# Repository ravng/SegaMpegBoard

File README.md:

# SegaMpegBoard!

Drop in replacement board for Sega Model 3 Mpeg board.
Tested on Scud Race but can't see why it would not work in other aracdes with the same mpeg board.

It uses the cheap DFPlayer MP3 module for soundtrack files and attiny84 for the communication.

A jumper is used to select different soundtracks (folders). 
Folder 1-4 plays the same sound track for each race track every time, while folder 5 will play songs in random order. 
If no jumper installed it will use folder "01", see source for details. 

IMPORTANT NOTE!
The attiny might need a clock calibration to work. 
I supposed it would be smart to add an external clock, but I didn't.
Fell free to modify the design yourself or search the web for attiny clock calibration.

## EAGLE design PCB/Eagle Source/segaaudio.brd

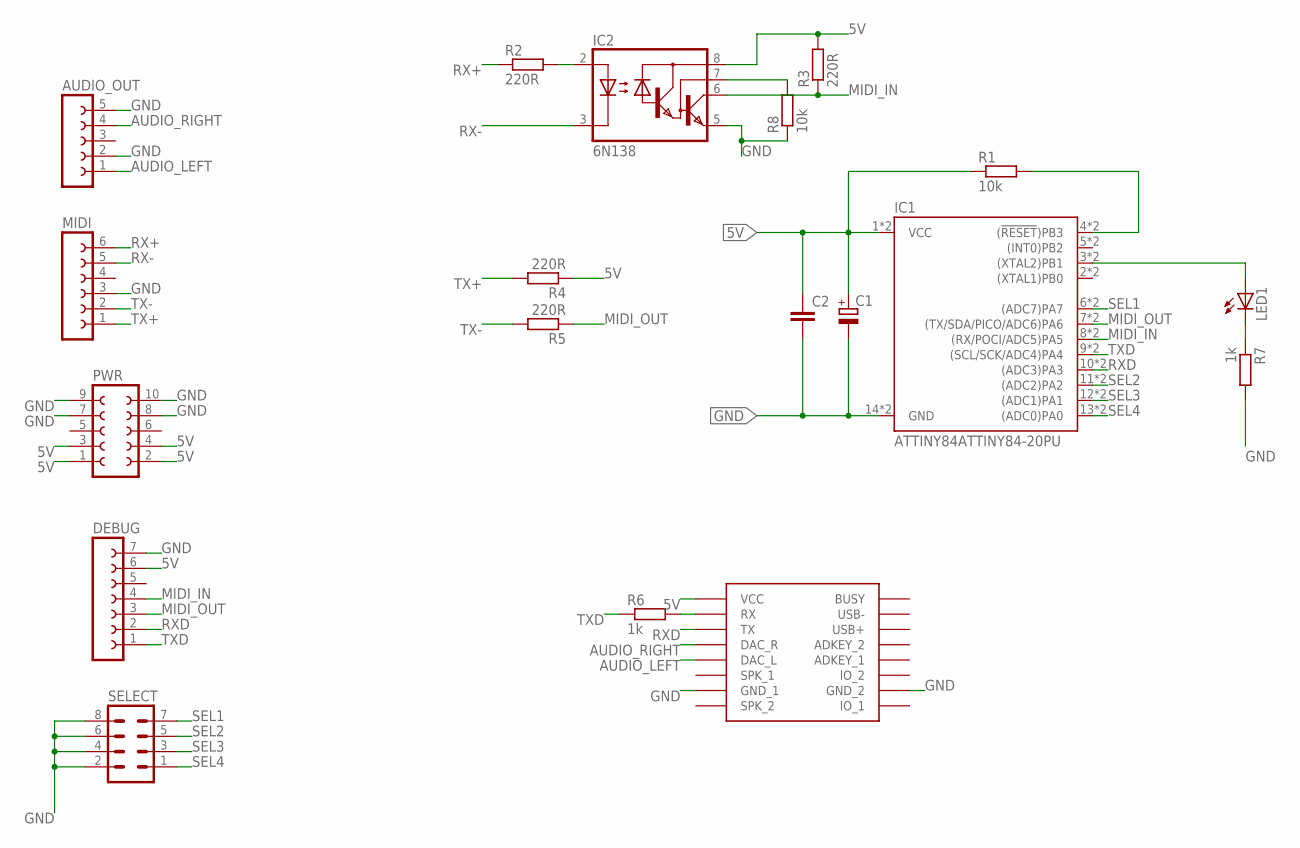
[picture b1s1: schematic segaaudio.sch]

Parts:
AUDIO_OUT: FE05-1
C1: CPOL-EUE5-10.5; E5-10,5
C2: C-EU050-025X075; C050-025X075
DEBUG: FE07-1; FE07
IC1: ATTINY84ATTINY84-20PU; DIP14
IC2: 6N138; DIL08
IC3: DFPLAYER
LED1: LED3MM
MIDI: FE06-1; FE06
PWR: FE05-2
R1, R8: 10k; 0309/12
R2, R3, R4, R5: 220R; 0309/12
R6, R7: 1k; 0309/12
SELECT: MA04-2

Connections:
5V: C1.+, C2.1, DEBUG.6, IC1.1 (VCC), IC1.1A (VCC), IC2.8 (VCC), IC3.VCC, PWR.1, PWR.2, PWR.3, PWR.4, R1.1, R3.2, R4.1
AUDIO_LEFT: AUDIO_OUT.1, IC3.DAC_L
AUDIO_RIGHT: AUDIO_OUT.4, IC3.DAC_R
GND: AUDIO_OUT.2, AUDIO_OUT.5, C1.-, C2.2, DEBUG.7, IC1.14 (GND), IC1.14A (GND), IC2.5 (GND), IC3.GND_1, IC3.GND_2, MIDI.3, PWR.7, PWR.8, PWR.9, PWR.10, R7.2, R8.1, SELECT.2, SELECT.4, SELECT.6, SELECT.8
MIDI_IN: DEBUG.4, IC1.8 ((RX/POCI/ADC5)PA5), IC1.8A ((RX/POCI/ADC5)PA5), IC2.6 (VO), R3.1
MIDI_OUT: DEBUG.3, IC1.7 ((TX/SDA/PICO/ADC6)PA6), IC1.7A ((TX/SDA/PICO/ADC6)PA6), R5.1
unnamed: IC1.4 ((!RESET!)PB3), IC1.4A ((!RESET!)PB3), R1.2
unnamed: IC2.2 (A), R2.2
unnamed: IC1.3 ((XTAL2)PB1), IC1.3A ((XTAL2)PB1), LED1.A
unnamed: LED1.K (C), R7.1
unnamed: IC3.RX, R6.2
unnamed: IC2.7 (VB), R8.2
RX+: MIDI.6, R2.1
RX-: IC2.3 (C), MIDI.5
RXD: DEBUG.2, IC1.10 ((ADC3)PA3), IC1.10A ((ADC3)PA3), IC3.TX
SEL1: IC1.6 ((ADC7)PA7), IC1.6A ((ADC7)PA7), SELECT.7
SEL2: IC1.11 ((ADC2)PA2), IC1.11A ((ADC2)PA2), SELECT.5
SEL3: IC1.12 ((ADC1)PA1), IC1.12A ((ADC1)PA1), SELECT.3
SEL4: IC1.13 ((ADC0)PA0), IC1.13A ((ADC0)PA0), SELECT.1
TX+: MIDI.1, R4.2
TX-: MIDI.2, R5.2
TXD: DEBUG.1, IC1.9 ((SCL/SCK/ADC4)PA4), IC1.9A ((SCL/SCK/ADC4)PA4), R6.1

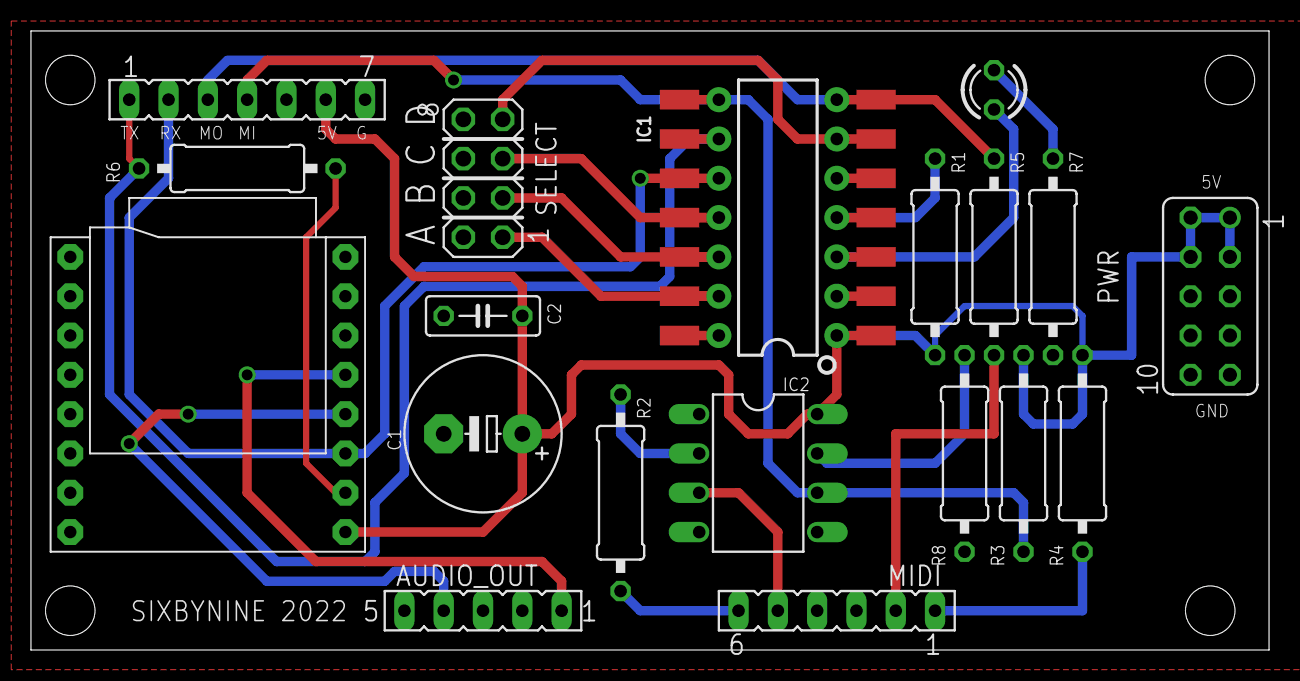
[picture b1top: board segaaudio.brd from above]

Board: 2 copper layers, 80.0 x 40.0 mm, 19 parts (0 on the bottom side), 22 nets.

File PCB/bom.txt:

Sega Mpeg Board BOM

C1:	10uF Capacitor polarized	
C2:	0.1uF Capacitor
LED1:	Any color led
R1:	10k *
R2:	220R
R3:	220R
R4:	220R
R5:	220R
R6:	1k
R7:	1k
R8:	10k *
IC1:	Attiny84 
IC2:	6N138 Opto Isolator
IC3:  DFPlayer module (suggest female header pins)
All connectors:	2.54mm Male Header pins




*(will most likely work perfectly fine without!)

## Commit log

2022-10-14 Intial release
2022-12-28 Working version
2022-12-28 Added precompiled firmware

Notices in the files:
parts and their libraries:
Ravn-Microcontroller: Licensing: Creative Commons ShareAlike 4.0 International - https://creativecommons.org/licenses/by-sa/4.0
